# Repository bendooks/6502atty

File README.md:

# 6502 Atty

A 6502 SBC with an ATMega as a contoller and monitor for the 6502.

This is an initial commit as PCBs are off for manufacture and not been tested. This includes the prototype firmware and the first cut of the firmware code.

The ATmega is probably the easiest MCU to get and program which is 5V tolerant. The 1284P is the current choice as the smaller memory versions are not much cheaper.

## Build notes for v1 rev1

- The 100UF capacitors are 16mm long so trying 47uF, layout change?

The LED resistors will probably need to be reduced to 680R or low as 506R depending on the LEDs being fitted.

The pull-up/pull-down resistors can be anywhere from 1K to 4K7, experiments with previous boards show 10K may not be suitable with certain variants of the 6052. Anything below 1K is probably going to have issues with current dissapation as that will be around 5mA per resistor. 

During test it was found that there seems to be a difference in operation dependong on how the PHi2 jumper is selected. If the PHI2O is used, we get proper operation but if CPU_CLK is seleted then the download code works but the code that is downloaded does not work.

## PCB updates (v1 rev2)

- Added J12 to route ~WE signal to the PGM/~WE to allow SRAM
  - Also requires a R/!W signal gated with PHI2 high
  - Added R~{W}ph signal for ROM
  - This new signal could also drive RAM ~WE and connect ~CS to A15
- Connected ROM's VPP signal to GND, if using SRAM, ties A14 to GND
- U9C's pins 9 and 10 swapped for routing
- U11's E1/E2 pins swapped for easier routing
- Transcription error from prototype, ROM_ACC should be from AND not NAND gate
  - Swao U8C for one of U10 spare gates
- RDY line missing pull-up resistor
- 74LS573 replaced with 74LS574
  - 573 latches when Load is high, and our enable is low
  - 574 will load on rising edge of load pin, so should work
- Made PCB smaller, moved a few LEDs and things around to make this work
- Dropped 1K series drive resistor for the crystal
  - ATMega will not start if this resistor is there

TODO:
- Serial converter is rotated 180deg to the actual unit
- Recomendation for AVRisp is to use 10K on ATMega's nRESET, so changed

Currently unknown issues:
- Firmware only works with PHI2 jumper on PHI2out
  - can't see any scoped difference between CPUclk and PHI2out

# Firmware

The firmware is currently in development. To build, you will need at-least avr-gcc and the relevant libraries and is currently only being tested on Linux (Debian). Once built, download to the ATMega using something like avrdude.

## Revision information

The original prototype version was built on a perfboard, and not released.

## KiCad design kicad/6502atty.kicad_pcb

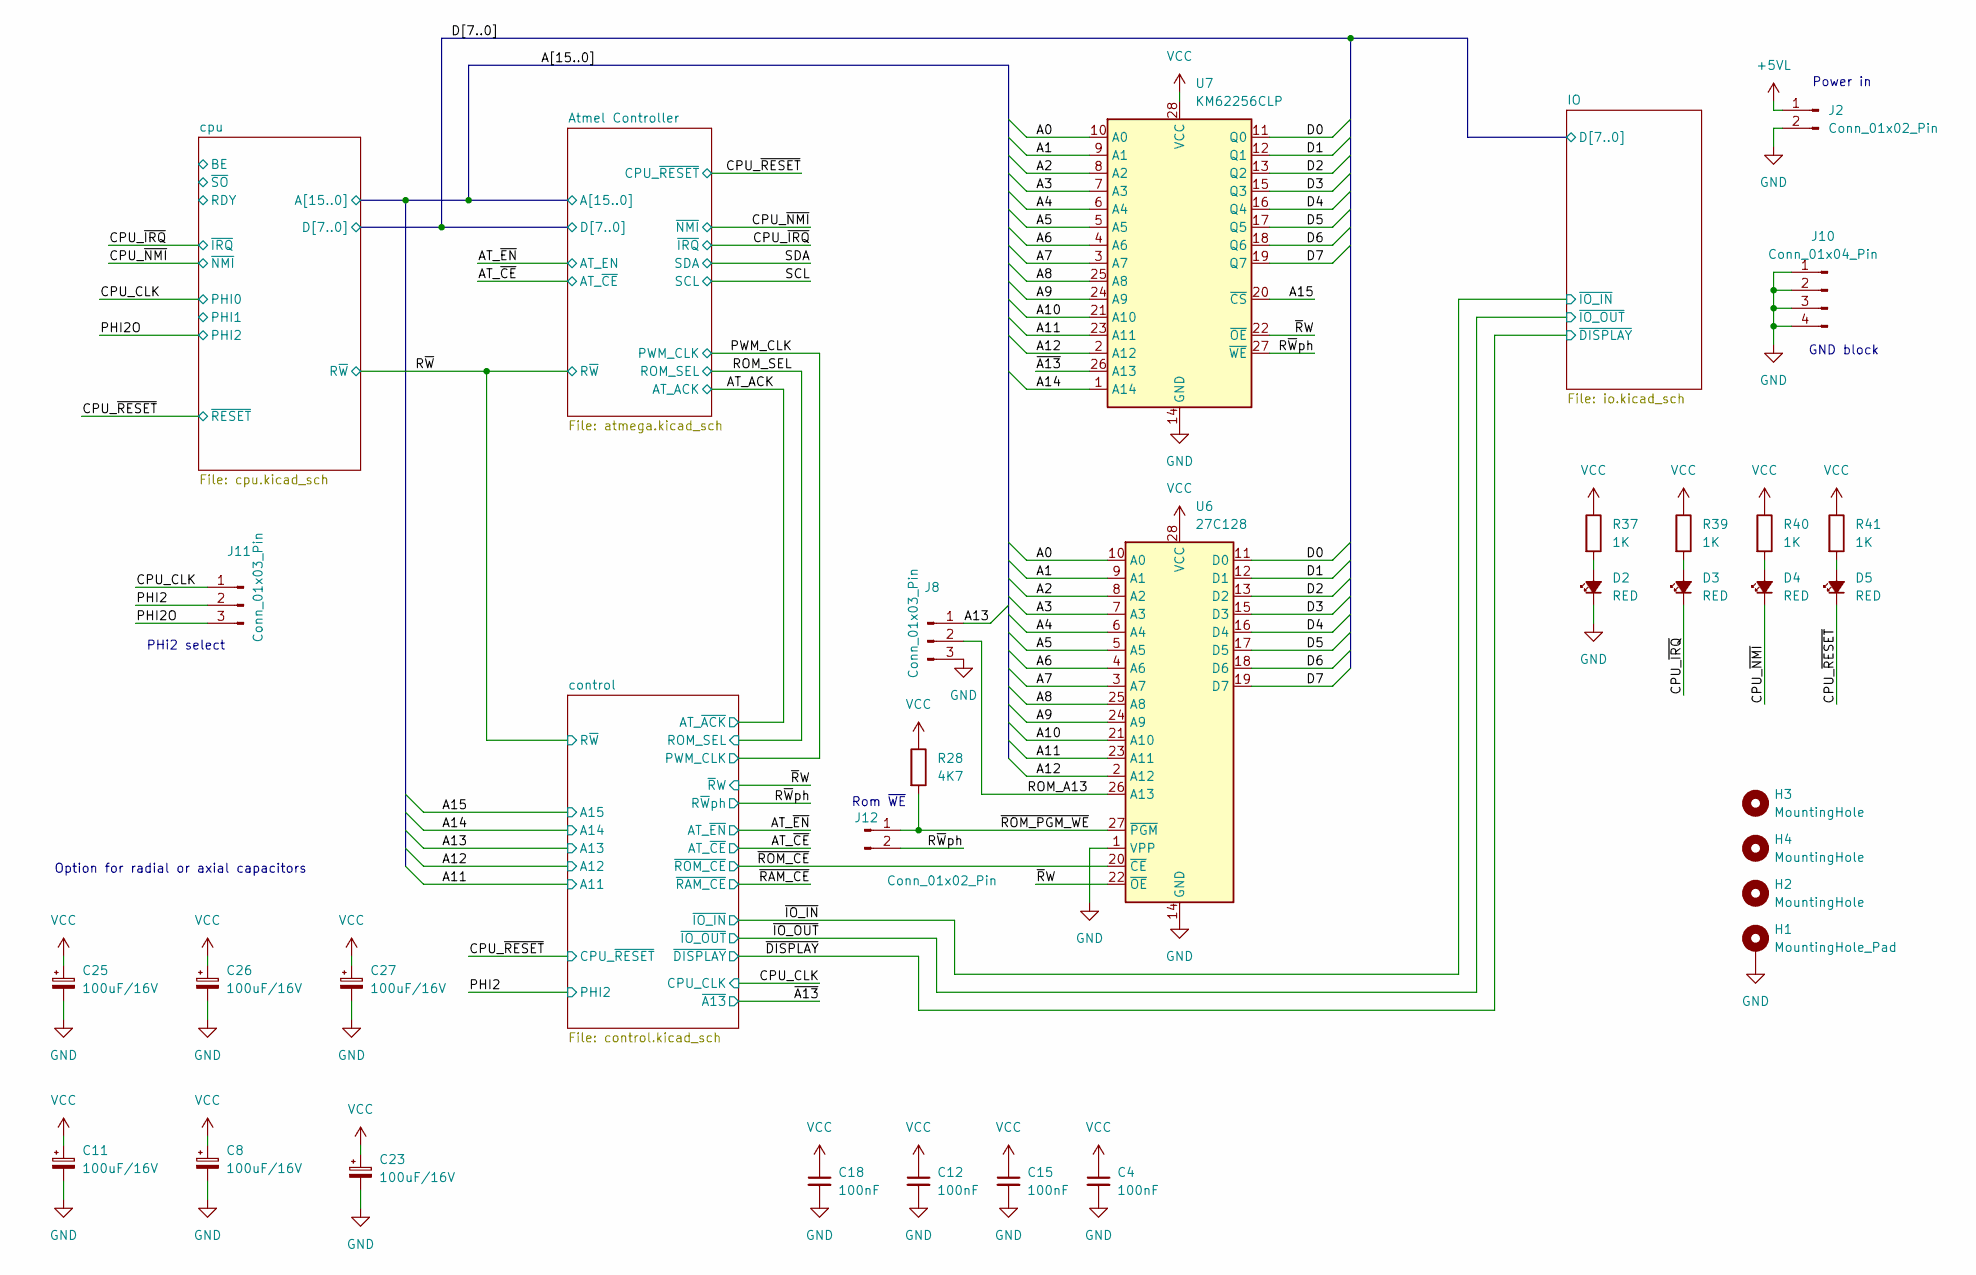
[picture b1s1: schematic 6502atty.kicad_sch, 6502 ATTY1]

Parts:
C4, C12, C15, C18: 100nF; C_Disc_D4.3mm_W1.9mm_P5.00mm
C8, C11, C23: 100uF/16V; CP_Axial_L10.0mm_D6.0mm_P15.00mm_Horizontal
C25, C26, C27: 100uF/16V; CP_Radial_D6.3mm_P2.50mm
D2, D3, D4, D5: RED; LED_D5.0mm
H1: MountingHole_Pad; MountingHole_3.2mm_M3_Pad
H2, H3, H4: MountingHole; MountingHole_3.2mm_M3_Pad
J2: Conn_01x02_Pin; Molex_KK-254_AE-6410-02A_1x02_P2.54mm_Vertical
J8, J11: Conn_01x03_Pin; PinHeader_1x03_P2.54mm_Vertical
J10: Conn_01x04_Pin; PinHeader_1x04_P2.54mm_Vertical
J12: Conn_01x02_Pin; PinHeader_1x02_P2.54mm_Vertical
R28: 4K7; R_Axial_DIN0207_L6.3mm_D2.5mm_P10.16mm_Horizontal
R37, R39, R40: 1K; R_Axial_DIN0207_L6.3mm_D2.5mm_P10.16mm_Horizontal
R41: 1K; R_Axial_DIN0207_L6.3mm_D2.5mm_P2.54mm_Vertical
U6: 27C128; DIP-28_W15.24mm
U7: KM62256CLP; DIP-28_W15.24mm

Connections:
+5VL: J2.1; also elsewhere on the board
/A0: U6.10 (A0), U7.10 (A0); also elsewhere on the board
/A1: U6.9 (A1), U7.9 (A1); also elsewhere on the board
/A2: U6.8 (A2), U7.8 (A2); also elsewhere on the board
/A3: U6.7 (A3), U7.7 (A3); also elsewhere on the board
/A4: U6.6 (A4), U7.6 (A4); also elsewhere on the board
/A5: U6.5 (A5), U7.5 (A5); also elsewhere on the board
/A6: U6.4 (A6), U7.4 (A6); also elsewhere on the board
/A7: U6.3 (A7), U7.3 (A7); also elsewhere on the board
/A8: U6.25 (A8), U7.25 (A8); also elsewhere on the board
/A9: U6.24 (A9), U7.24 (A9); also elsewhere on the board
/A10: U6.21 (A10), U7.21 (A10); also elsewhere on the board
/A11: U6.23 (A11), U7.23 (A11); also elsewhere on the board
/A12: U6.2 (A12), U7.2 (A12); also elsewhere on the board
/A13: J8.1; also elsewhere on the board
/A14: U7.1 (A14); also elsewhere on the board
/A15: U7.20 (~CS); also elsewhere on the board
/CPU_CLK: J11.1; also elsewhere on the board
/CPU_~IRQ: D3.1 (K); also elsewhere on the board
/CPU_~NMI: D4.1 (K); also elsewhere on the board
/CPU_~RESET: D5.1 (K); also elsewhere on the board
/D0: U6.11 (D0), U7.11 (Q0); also elsewhere on the board
/D1: U6.12 (D1), U7.12 (Q1); also elsewhere on the board
/D2: U6.13 (D2), U7.13 (Q2); also elsewhere on the board
/D3: U6.15 (D3), U7.15 (Q3); also elsewhere on the board
/D4: U6.16 (D4), U7.16 (Q4); also elsewhere on the board
/D5: U6.17 (D5), U7.17 (Q5); also elsewhere on the board
/D6: U6.18 (D6), U7.18 (Q6); also elsewhere on the board
/D7: U6.19 (D7), U7.19 (Q7); also elsewhere on the board
/PHI2: J11.2; also elsewhere on the board
/PHI2O: J11.3; also elsewhere on the board
/ROM_A13: J8.2, U6.26 (A13)
/R~Wph: J12.2, U7.27 (~WE); also elsewhere on the board
/~A13: U7.26 (A13); also elsewhere on the board
/~ROM_CE: U6.20 (~CE); also elsewhere on the board
/~ROM_PGM_WE: J12.1, R28.2, U6.27 (~PGM)
/~RW: U6.22 (~OE), U7.22 (~OE); also elsewhere on the board
GND: C4.2, C8.2, C11.2, C12.2, C15.2, C18.2, C23.2, C25.2, C26.2, C27.2, D2.1 (K), H1.1, J2.2, J8.3, J10.1, J10.2, J10.3, J10.4, U6.1 (VPP), U6.14 (GND), U7.14 (GND); also elsewhere on the board
unnamed: D2.2 (A), R37.2
unnamed: D3.2 (A), R39.2
unnamed: D4.2 (A), R40.2
unnamed: D5.2 (A), R41.2
VCC: C4.1, C8.1, C11.1, C12.1, C15.1, C18.1, C23.1, C25.1, C26.1, C27.1, R28.1, R37.1, R39.1, R40.1, R41.1, U6.28 (VCC), U7.28 (VCC); also elsewhere on the board

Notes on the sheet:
Power in
GND block
Option for radial or axial capacitors
PHi2 select
Rom ~{WE}

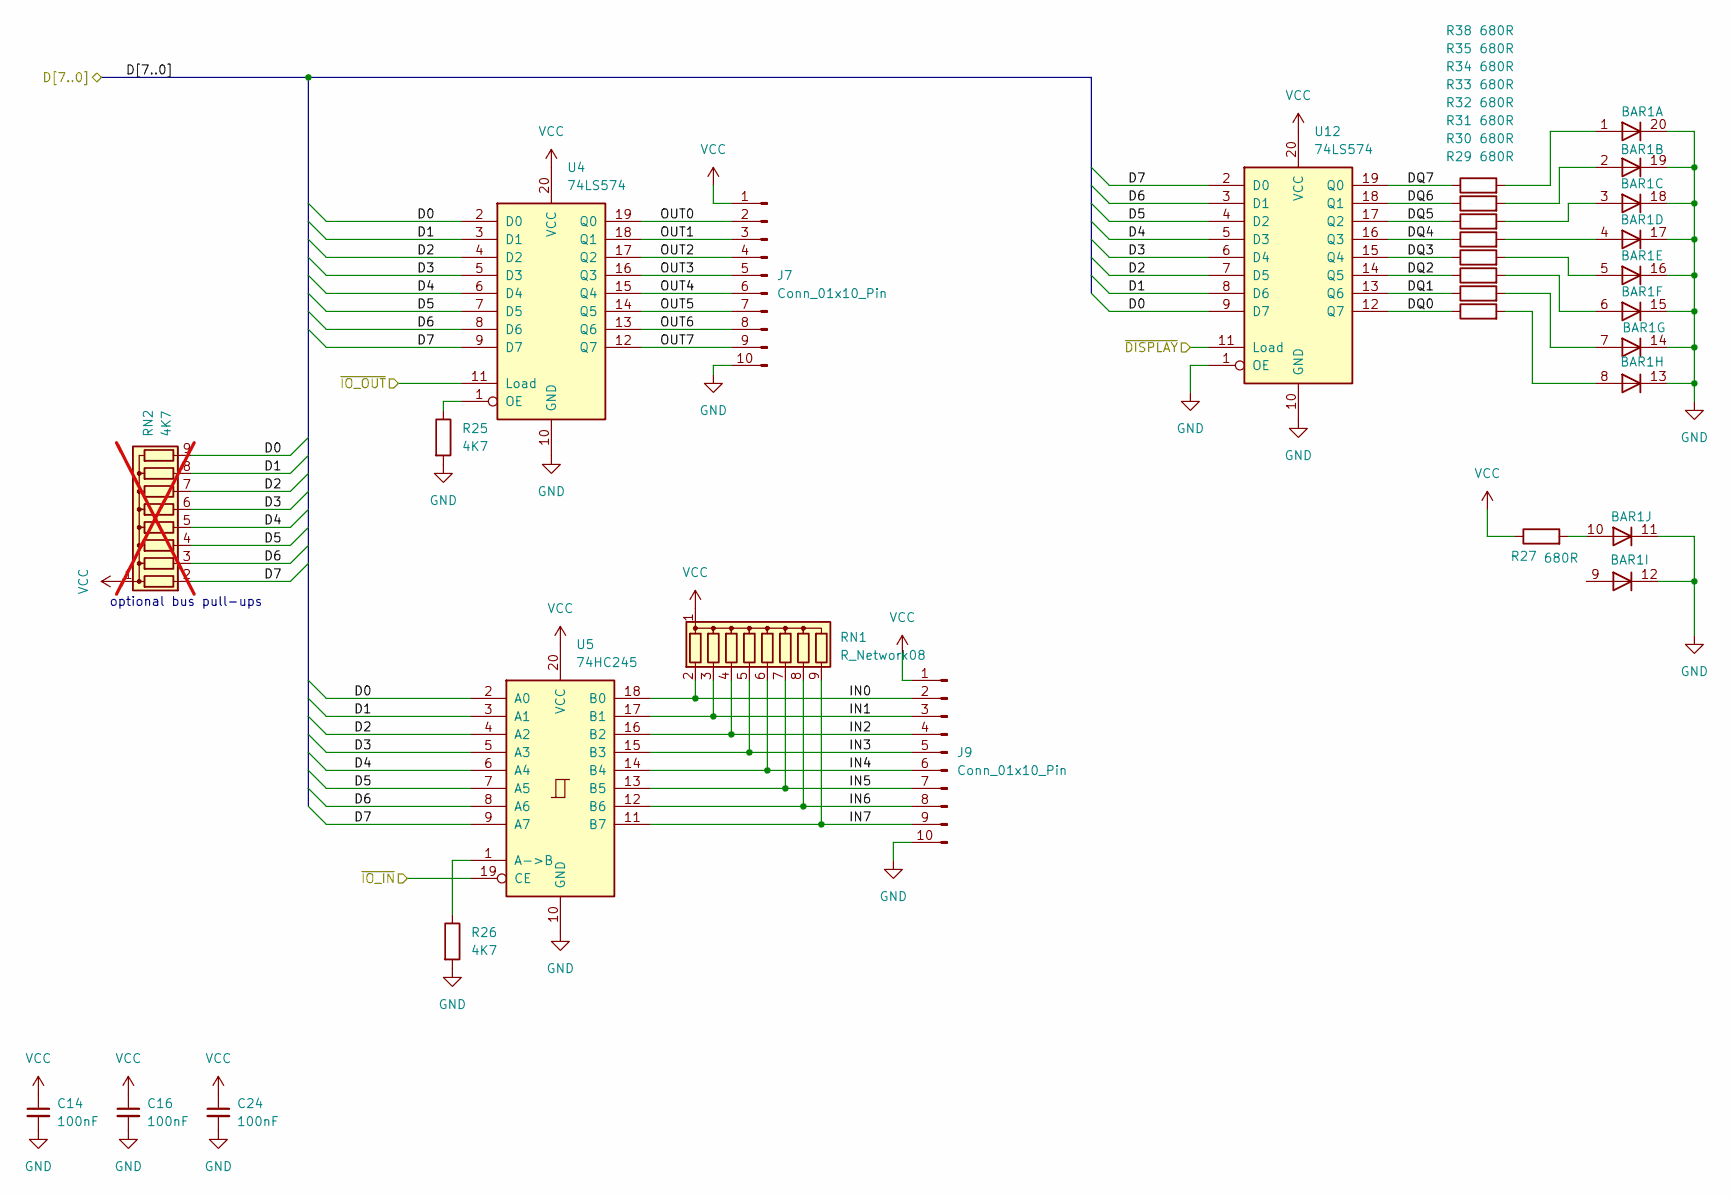
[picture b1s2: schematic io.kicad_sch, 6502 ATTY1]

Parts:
BAR1: HDSP-4850
C14, C16, C24: 100nF; C_Disc_D4.3mm_W1.9mm_P5.00mm
J7, J9: Conn_01x10_Pin; PinHeader_1x10_P2.54mm_Vertical
R25, R26: 4K7; R_Axial_DIN0207_L6.3mm_D2.5mm_P10.16mm_Horizontal
R27, R29, R30, R31, R32, R33, R34, R35, R38: 680R; R_Axial_DIN0207_L6.3mm_D2.5mm_P2.54mm_Vertical
RN1: R_Network08; R_Array_SIP9
RN2: 4K7; R_Array_SIP9; not fitted
U4, U12: 74LS574; DIP-20_W7.62mm
U5: 74HC245; DIP-20_W7.62mm

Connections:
/D0: RN2.9 (R8), U4.2 (D0), U5.2 (A0), U12.9 (D7); also elsewhere on the board
/D1: RN2.8 (R7), U4.3 (D1), U5.3 (A1), U12.8 (D6); also elsewhere on the board
/D2: RN2.7 (R6), U4.4 (D2), U5.4 (A2), U12.7 (D5); also elsewhere on the board
/D3: RN2.6 (R5), U4.5 (D3), U5.5 (A3), U12.6 (D4); also elsewhere on the board
/D4: RN2.5 (R4), U4.6 (D4), U5.6 (A4), U12.5 (D3); also elsewhere on the board
/D5: RN2.4 (R3), U4.7 (D5), U5.7 (A5), U12.4 (D2); also elsewhere on the board
/D6: RN2.3 (R2), U4.8 (D6), U5.8 (A6), U12.3 (D1); also elsewhere on the board
/D7: RN2.2 (R1), U4.9 (D7), U5.9 (A7), U12.2 (D0); also elsewhere on the board
/IO/DQ0: R29.1, U12.12 (Q7)
/IO/DQ1: R30.1, U12.13 (Q6)
/IO/DQ2: R31.1, U12.14 (Q5)
/IO/DQ3: R32.1, U12.15 (Q4)
/IO/DQ4: R33.1, U12.16 (Q3)
/IO/DQ5: R34.1, U12.17 (Q2)
/IO/DQ6: R35.1, U12.18 (Q1)
/IO/DQ7: R38.1, U12.19 (Q0)
/IO/IN0: J9.2, RN1.2 (R1), U5.18 (B0)
/IO/IN1: J9.3, RN1.3 (R2), U5.17 (B1)
/IO/IN2: J9.4, RN1.4 (R3), U5.16 (B2)
/IO/IN3: J9.5, RN1.5 (R4), U5.15 (B3)
/IO/IN4: J9.6, RN1.6 (R5), U5.14 (B4)
/IO/IN5: J9.7, RN1.7 (R6), U5.13 (B5)
/IO/IN6: J9.8, RN1.8 (R7), U5.12 (B6)
/IO/IN7: J9.9, RN1.9 (R8), U5.11 (B7)
/IO/OUT0: J7.2, U4.19 (Q0)
/IO/OUT1: J7.3, U4.18 (Q1)
/IO/OUT2: J7.4, U4.17 (Q2)
/IO/OUT3: J7.5, U4.16 (Q3)
/IO/OUT4: J7.6, U4.15 (Q4)
/IO/OUT5: J7.7, U4.14 (Q5)
/IO/OUT6: J7.8, U4.13 (Q6)
/IO/OUT7: J7.9, U4.12 (Q7)
/~DISPLAY: U12.11 (Load); also elsewhere on the board
/~IO_IN: U5.19 (CE); also elsewhere on the board
/~IO_OUT: U4.11 (Load); also elsewhere on the board
GND: BAR1.11 (K), BAR1.12 (K), BAR1.13 (K), BAR1.14 (K), BAR1.15 (K), BAR1.16 (K), BAR1.17 (K), BAR1.18 (K), BAR1.19 (K), BAR1.20 (K), C14.2, C16.2, C24.2, J7.10, J9.10, R25.2, R26.2, U4.10 (GND), U5.10 (GND), U12.1 (OE), U12.10 (GND); also elsewhere on the board
unnamed: BAR1.1 (A), R38.2
unnamed: BAR1.2 (A), R35.2
unnamed: BAR1.3 (A), R34.2
unnamed: BAR1.4 (A), R33.2
unnamed: BAR1.5 (A), R32.2
unnamed: BAR1.6 (A), R31.2
unnamed: BAR1.7 (A), R30.2
unnamed: BAR1.8 (A), R29.2
unnamed: BAR1.10 (A), R27.2
unnamed: R25.1, U4.1 (OE)
unnamed: R26.1, U5.1 (A->B)
VCC: C14.1, C16.1, C24.1, J7.1, J9.1, R27.1, RN1.1 (common), RN2.1 (common), U4.20 (VCC), U5.20 (VCC), U12.20 (VCC); also elsewhere on the board

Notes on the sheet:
optional bus pull-ups

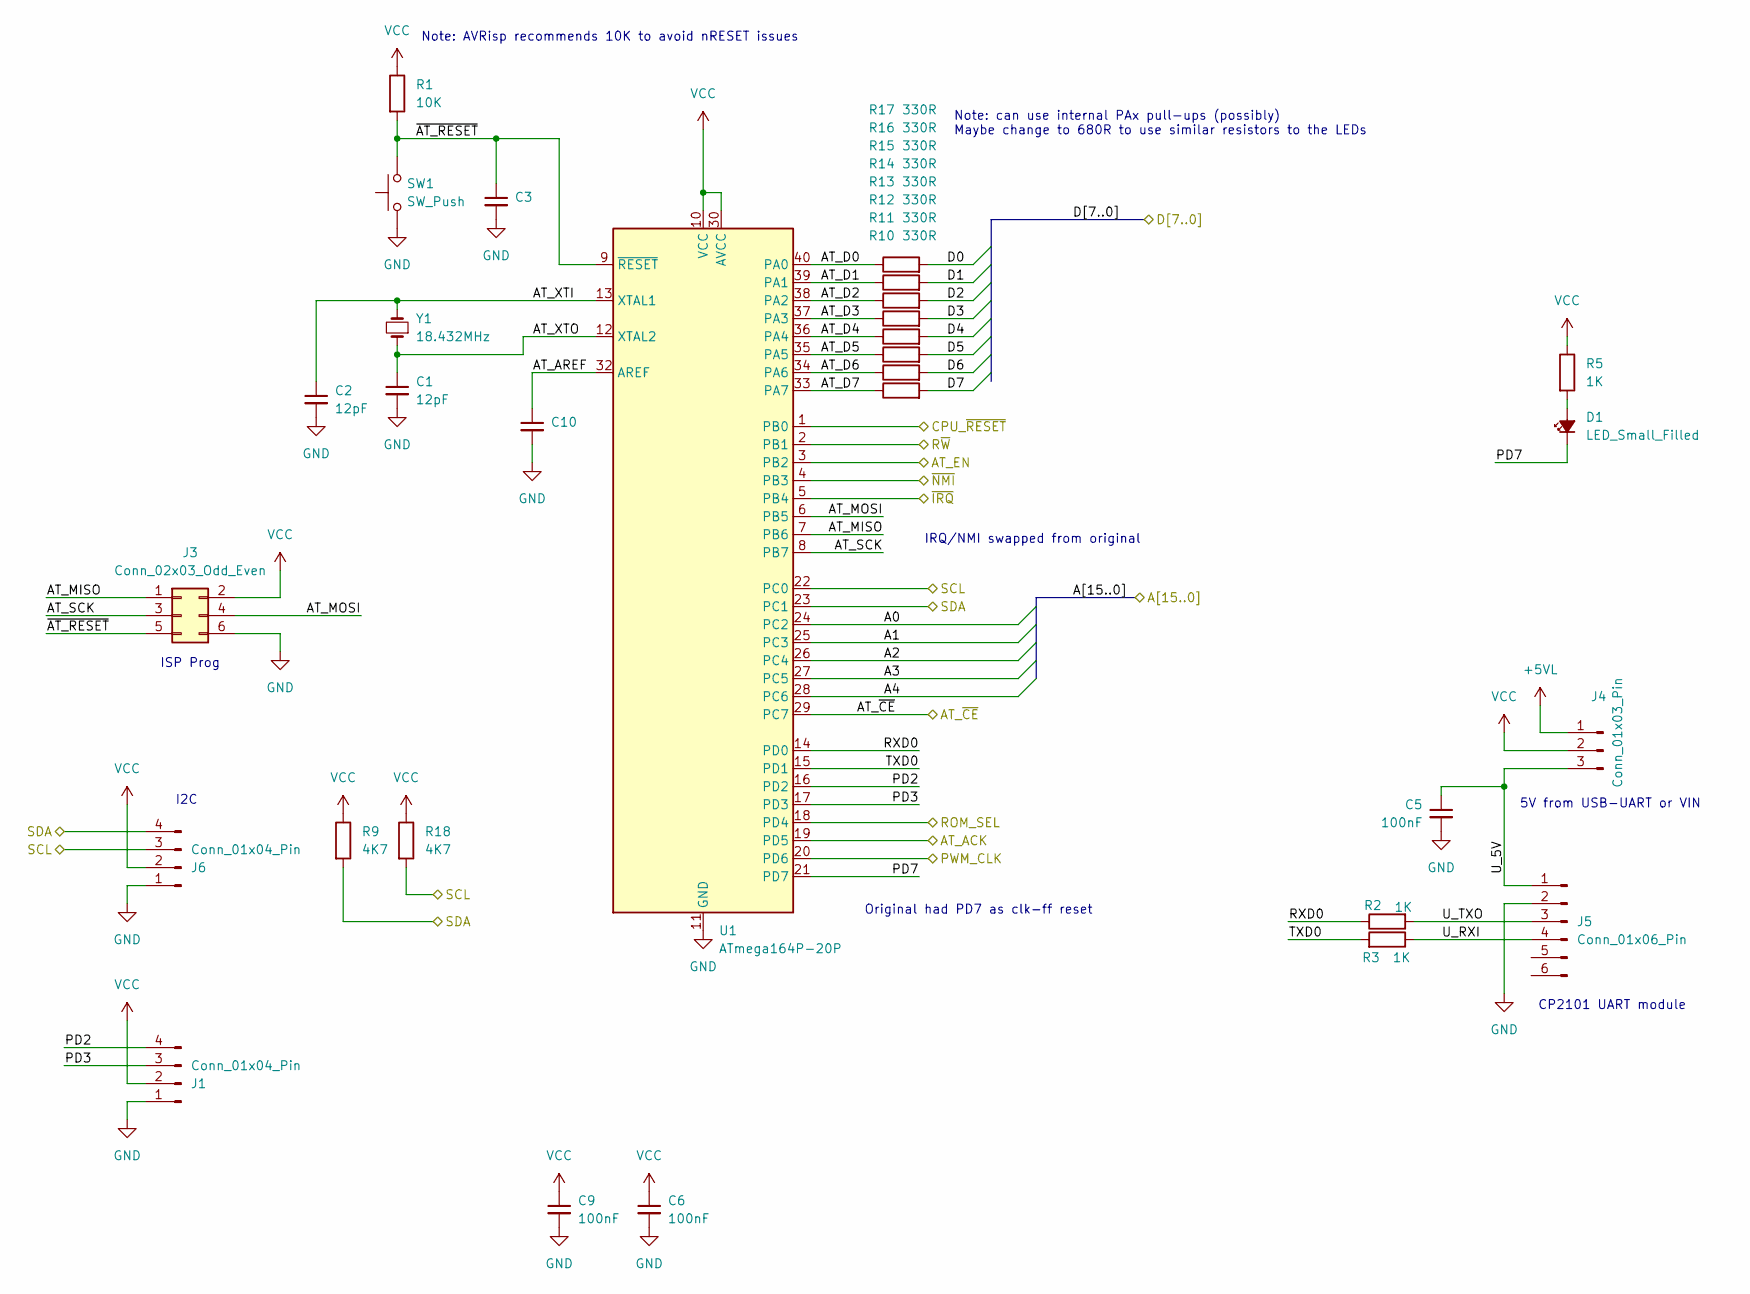
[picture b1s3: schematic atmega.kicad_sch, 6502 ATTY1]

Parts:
C1, C2: 12pF; C_Disc_D3.4mm_W2.1mm_P2.50mm
C3, C10: C_Disc_D4.3mm_W1.9mm_P5.00mm
C5, C6, C9: 100nF; C_Disc_D4.3mm_W1.9mm_P5.00mm
D1: LED_Small_Filled; LED_D5.0mm
J1: Conn_01x04_Pin; PinHeader_1x04_P2.54mm_Vertical
J3: Conn_02x03_Odd_Even; PinHeader_2x03_P2.54mm_Vertical
J4: Conn_01x03_Pin; PinHeader_1x03_P2.54mm_Vertical
J5: Conn_01x06_Pin; PinHeader_1x06_P2.54mm_Vertical
J6: Conn_01x04_Pin; PinSocket_1x04_P2.54mm_Vertical
R1: 10K; R_Axial_DIN0207_L6.3mm_D2.5mm_P2.54mm_Vertical
R2, R3, R5: 1K; R_Axial_DIN0207_L6.3mm_D2.5mm_P10.16mm_Horizontal
R9, R18: 4K7; R_Axial_DIN0207_L6.3mm_D2.5mm_P10.16mm_Horizontal
R10, R11, R12, R13, R14, R15, R16, R17: 330R; R_Axial_DIN0207_L6.3mm_D2.5mm_P10.16mm_Horizontal
SW1: SW_Push; SW_TH_Tactile_Omron_B3F-10xx
U1: ATmega164P-20P; DIP-40_W15.24mm
Y1: 18.432MHz; Crystal_HC49-4H_Vertical

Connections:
+5VL: J4.1; also elsewhere on the board
/A0: U1.24 (PC2); also elsewhere on the board
/A1: U1.25 (PC3); also elsewhere on the board
/A2: U1.26 (PC4); also elsewhere on the board
/A3: U1.27 (PC5); also elsewhere on the board
/A4: U1.28 (PC6); also elsewhere on the board
/AT_ACK: U1.19 (PD5); also elsewhere on the board
/AT_~CE: U1.29 (PC7); also elsewhere on the board
/AT_~EN: U1.3 (PB2); also elsewhere on the board
/Atmel Controller/AT_AREF: C10.1, U1.32 (AREF)
/Atmel Controller/AT_D0: R17.1, U1.40 (PA0)
/Atmel Controller/AT_D1: R16.1, U1.39 (PA1)
/Atmel Controller/AT_D2: R15.1, U1.38 (PA2)
/Atmel Controller/AT_D3: R14.1, U1.37 (PA3)
/Atmel Controller/AT_D4: R13.1, U1.36 (PA4)
/Atmel Controller/AT_D5: R12.1, U1.35 (PA5)
/Atmel Controller/AT_D6: R11.1, U1.34 (PA6)
/Atmel Controller/AT_D7: R10.1, U1.33 (PA7)
/Atmel Controller/AT_MISO: J3.1, U1.7 (PB6)
/Atmel Controller/AT_MOSI: J3.4, U1.6 (PB5)
/Atmel Controller/AT_SCK: J3.3, U1.8 (PB7)
/Atmel Controller/AT_XTI: C2.1, U1.13 (XTAL1), Y1.2
/Atmel Controller/AT_XTO: C1.1, U1.12 (XTAL2), Y1.1
/Atmel Controller/PD2: J1.4, U1.16 (PD2)
/Atmel Controller/PD3: J1.3, U1.17 (PD3)
/Atmel Controller/PD7: D1.1 (K), U1.21 (PD7)
/Atmel Controller/RXD0: R2.1, U1.14 (PD0)
/Atmel Controller/TXD0: R3.2, U1.15 (PD1)
/Atmel Controller/U_5V: C5.1, J4.3, J5.1
/Atmel Controller/U_RXI: J5.4, R3.1
/Atmel Controller/U_TXO: J5.3, R2.2
/Atmel Controller/~AT_RESET: C3.1, J3.5, R1.2, SW1.2, U1.9 (~RESET)
/CPU_~IRQ: U1.5 (PB4); also elsewhere on the board
/CPU_~NMI: U1.4 (PB3); also elsewhere on the board
/CPU_~RESET: U1.1 (PB0); also elsewhere on the board
/D0: R17.2; also elsewhere on the board
/D1: R16.2; also elsewhere on the board
/D2: R15.2; also elsewhere on the board
/D3: R14.2; also elsewhere on the board
/D4: R13.2; also elsewhere on the board
/D5: R12.2; also elsewhere on the board
/D6: R11.2; also elsewhere on the board
/D7: R10.2; also elsewhere on the board
/PWM_CLK: U1.20 (PD6); also elsewhere on the board
/ROM_SEL: U1.18 (PD4); also elsewhere on the board
/R~W: U1.2 (PB1); also elsewhere on the board
/SCL: J6.3, R18.2, U1.22 (PC0)
/SDA: J6.4, R9.2, U1.23 (PC1)
GND: C1.2, C2.2, C3.2, C5.2, C6.2, C9.2, C10.2, J1.1, J3.6, J5.2, J6.1, SW1.1, U1.11 (GND), U1.31 (GND); also elsewhere on the board
unnamed: D1.2 (A), R5.2
VCC: C6.1, C9.1, J1.2, J3.2, J4.2, J6.2, R1.1, R5.1, R9.1, R18.1, U1.10 (VCC), U1.30 (AVCC); also elsewhere on the board

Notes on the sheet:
ISP Prog
I2C
5V from USB-UART or VIN
Original had PD7 as clk-ff reset
IRQ/NMI swapped from original
Note: can use internal PAx pull-ups (possibly) Maybe change to 680R to use similar resistors to the LEDs
CP2101 UART module
Note: AVRisp recommends 10K to avoid nRESET issues

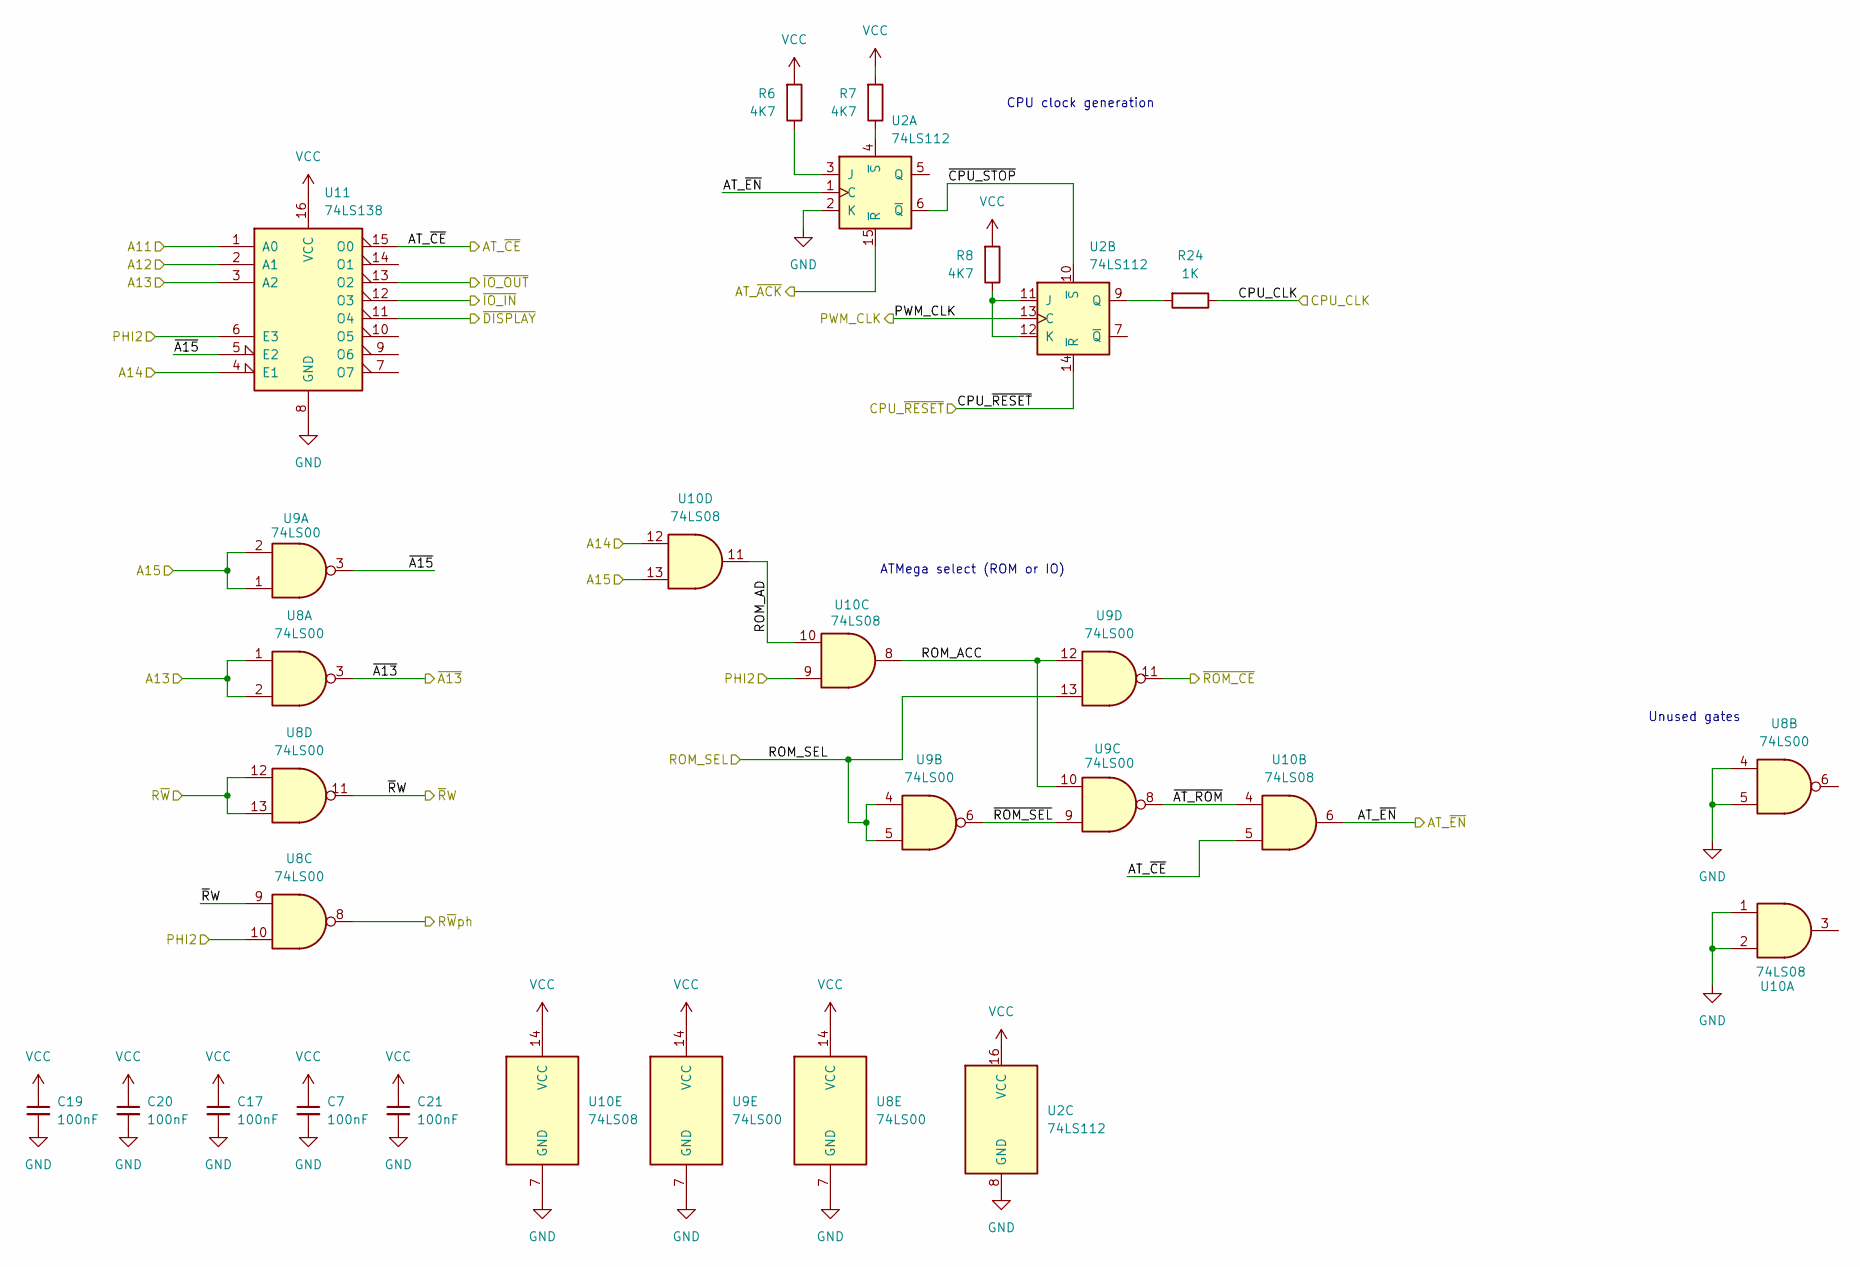
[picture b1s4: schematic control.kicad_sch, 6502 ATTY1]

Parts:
C7, C17, C19, C20, C21: 100nF; C_Disc_D4.3mm_W1.9mm_P5.00mm
R6, R7, R8: 4K7; R_Axial_DIN0207_L6.3mm_D2.5mm_P10.16mm_Horizontal
R24: 1K; R_Axial_DIN0207_L6.3mm_D2.5mm_P10.16mm_Horizontal
U2: 74LS112; DIP-16_W7.62mm
U8, U9: 74LS00; DIP-14_W7.62mm
U10: 74LS08; DIP-14_W7.62mm
U11: 74LS138; DIP-16_W7.62mm

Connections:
/A11: U11.1 (A0); also elsewhere on the board
/A12: U11.2 (A1); also elsewhere on the board
/A13: U8.1, U8.2, U11.3 (A2); also elsewhere on the board
/A14: U10.12, U11.4 (E1); also elsewhere on the board
/A15: U9.1, U9.2, U10.13; also elsewhere on the board
/AT_ACK: U2.15 (~R); also elsewhere on the board
/AT_~CE: U10.5, U11.15 (O0); also elsewhere on the board
/AT_~EN: U2.1 (C), U10.6; also elsewhere on the board
/CPU_CLK: R24.1; also elsewhere on the board
/CPU_~RESET: U2.14 (~R); also elsewhere on the board
/PHI2: U8.10, U10.9, U11.6 (E3); also elsewhere on the board
/PWM_CLK: U2.13 (C); also elsewhere on the board
/ROM_SEL: U9.4, U9.5, U9.13; also elsewhere on the board
/R~W: U8.12, U8.13; also elsewhere on the board
/R~Wph: U8.8; also elsewhere on the board
/control/ROM_ACC: U9.10, U9.12, U10.8
/control/ROM_AD: U10.10, U10.11
/control/~A15: U9.3, U11.5 (E2)
/control/~AT_ROM: U9.8, U10.4
/control/~CPU_STOP: U2.6 (~Q), U2.10 (~S)
/control/~ROM_SEL: U9.6, U9.9
/~A13: U8.3; also elsewhere on the board
/~DISPLAY: U11.11 (O4); also elsewhere on the board
/~IO_IN: U11.12 (O3); also elsewhere on the board
/~IO_OUT: U11.13 (O2); also elsewhere on the board
/~ROM_CE: U9.11; also elsewhere on the board
/~RW: U8.9, U8.11; also elsewhere on the board
GND: C7.2, C17.2, C19.2, C20.2, C21.2, U2.2 (K), U2.8 (GND), U8.4, U8.5, U8.7 (GND), U9.7 (GND), U10.1, U10.2, U10.7 (GND), U11.8 (GND); also elsewhere on the board
unnamed: R6.1, U2.3 (J)
unnamed: R7.1, U2.4 (~S)
unnamed: R8.1, U2.11 (J), U2.12 (K)
unnamed: R24.2, U2.9 (Q)
VCC: C7.1, C17.1, C19.1, C20.1, C21.1, R6.2, R7.2, R8.2, U2.16 (VCC), U8.14 (VCC), U9.14 (VCC), U10.14 (VCC), U11.16 (VCC); also elsewhere on the board

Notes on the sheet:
ATMega select (ROM or IO)
Unused gates
CPU clock generation

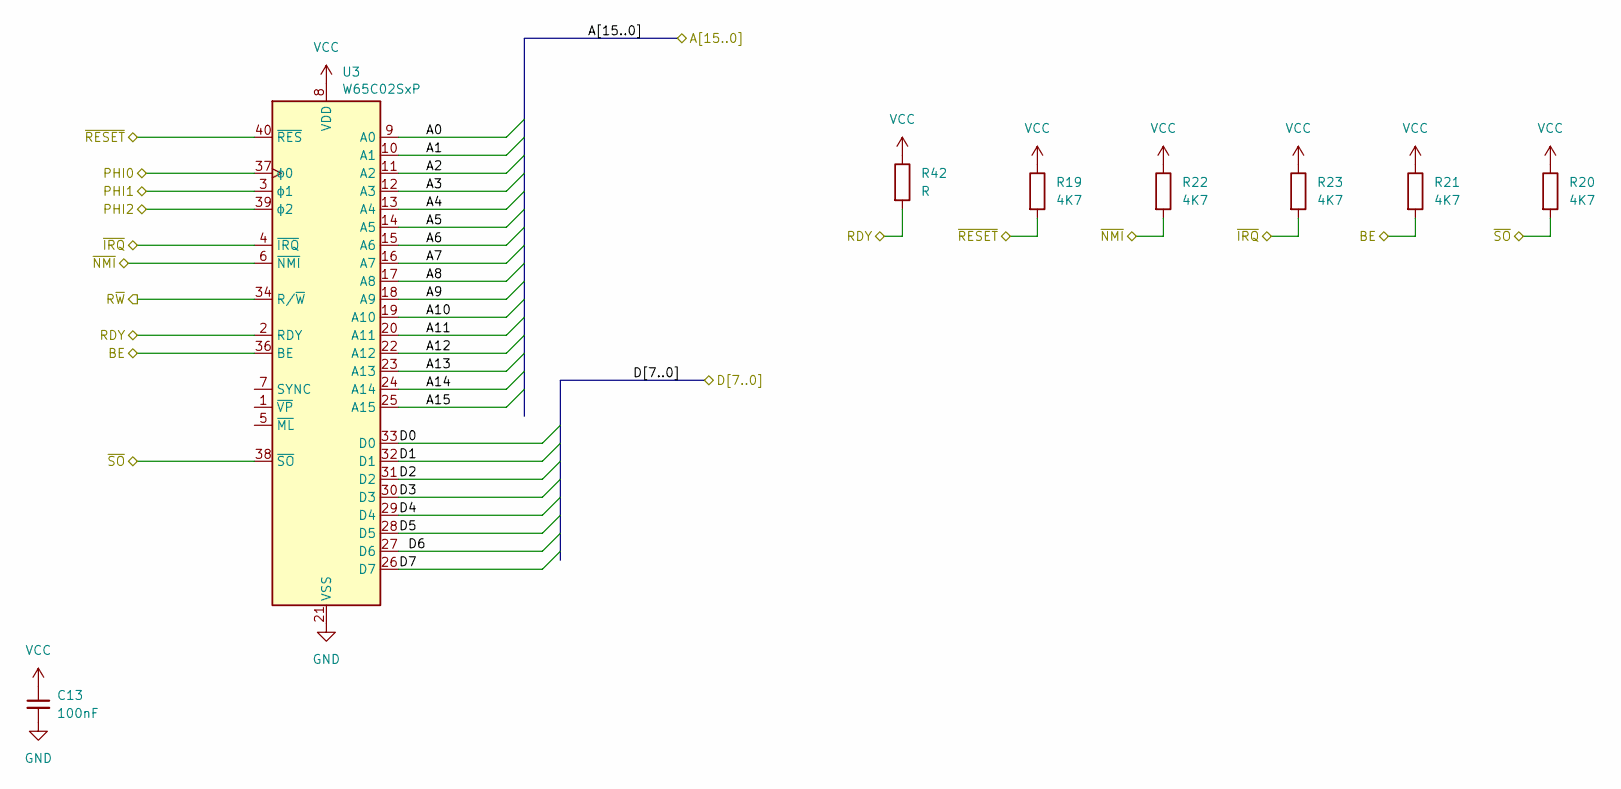
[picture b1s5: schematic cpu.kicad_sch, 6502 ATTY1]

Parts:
C13: 100nF; C_Disc_D4.3mm_W1.9mm_P5.00mm
R19, R20, R21, R22, R23: 4K7; R_Axial_DIN0207_L6.3mm_D2.5mm_P10.16mm_Horizontal
R42: R; R_Axial_DIN0207_L6.3mm_D2.5mm_P10.16mm_Horizontal
U3: W65C02SxP; DIP-40_W15.24mm

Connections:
/A0: U3.9 (A0); also elsewhere on the board
/A1: U3.10 (A1); also elsewhere on the board
/A2: U3.11 (A2); also elsewhere on the board
/A3: U3.12 (A3); also elsewhere on the board
/A4: U3.13 (A4); also elsewhere on the board
/A5: U3.14 (A5); also elsewhere on the board
/A6: U3.15 (A6); also elsewhere on the board
/A7: U3.16 (A7); also elsewhere on the board
/A8: U3.17 (A8); also elsewhere on the board
/A9: U3.18 (A9); also elsewhere on the board
/A10: U3.19 (A10); also elsewhere on the board
/A11: U3.20 (A11); also elsewhere on the board
/A12: U3.22 (A12); also elsewhere on the board
/A13: U3.23 (A13); also elsewhere on the board
/A14: U3.24 (A14); also elsewhere on the board
/A15: U3.25 (A15); also elsewhere on the board
/CPU_CLK: U3.37 (ϕ0); also elsewhere on the board
/CPU_~IRQ: R23.2, U3.4 (~IRQ); also elsewhere on the board
/CPU_~NMI: R22.2, U3.6 (~NMI); also elsewhere on the board
/CPU_~RESET: R19.2, U3.40 (~RES); also elsewhere on the board
/D0: U3.33 (D0); also elsewhere on the board
/D1: U3.32 (D1); also elsewhere on the board
/D2: U3.31 (D2); also elsewhere on the board
/D3: U3.30 (D3); also elsewhere on the board
/D4: U3.29 (D4); also elsewhere on the board
/D5: U3.28 (D5); also elsewhere on the board
/D6: U3.27 (D6); also elsewhere on the board
/D7: U3.26 (D7); also elsewhere on the board
/PHI2O: U3.39 (ϕ2); also elsewhere on the board
/R~W: U3.34 (R/~W); also elsewhere on the board
/cpu/BE: R21.2, U3.36 (BE)
/cpu/PHI1: U3.3 (ϕ1)
/cpu/RDY: R42.2, U3.2 (RDY)
/cpu/~SO: R20.2, U3.38 (~SO)
GND: C13.2, U3.21 (VSS); also elsewhere on the board
VCC: C13.1, R19.1, R20.1, R21.1, R22.1, R23.1, R42.1, U3.8 (VDD); also elsewhere on the board

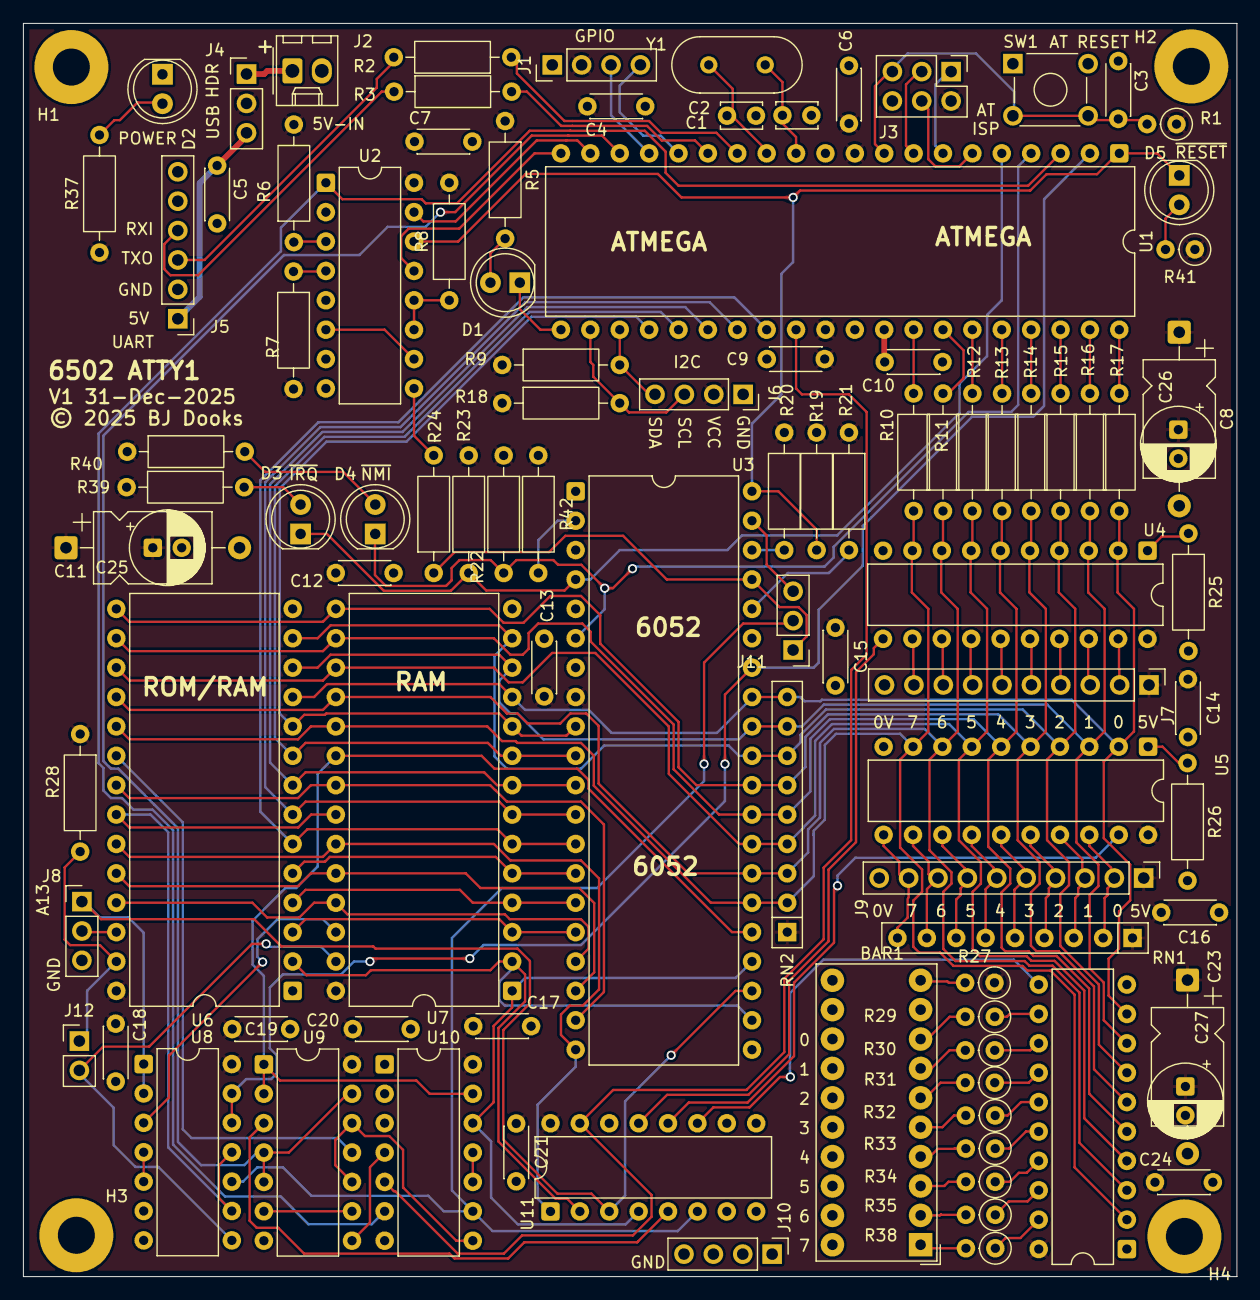
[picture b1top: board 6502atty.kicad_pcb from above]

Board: 2 copper layers, 104.9 x 108.3 mm, 104 parts (0 on the bottom side), 126 nets.

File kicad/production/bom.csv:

Designator,Footprint,Quantity,Value,LCSC Part #
BAR1,HDSP-4850,1,HDSP-4850,
"C1, C2",C_Disc_D3.4mm_W2.1mm_P2.50mm,2,12pF,
"C10, C3",C_Disc_D4.3mm_W1.9mm_P5.00mm,2,~,
"C11, C22, C23, C8",CP_Axial_L10.0mm_D6.0mm_P15.00mm_Horizontal,4,100uF/16V,
"C12, C13, C14, C15, C16, C17, C18, C19, C20, C21, C24, C4, C5, C6, C7, C9",C_Disc_D4.3mm_W1.9mm_P5.00mm,16,100nF,
D1,LED_D5.0mm,1,LED_Small_Filled,
"D2, D3, D4, D5",LED_D5.0mm,4,RED,
"J1, J10",PinHeader_1x04_P2.54mm_Vertical,2,Conn_01x04_Pin,
"J11, J4, J8",PinHeader_1x03_P2.54mm_Vertical,3,Conn_01x03_Pin,
J12,PinHeader_1x02_P2.54mm_Vertical,1,Conn_01x02_Pin,
J2,Molex_KK-254_AE-6410-02A_1x02_P2.54mm_Vertical,1,Conn_01x02_Pin,
J3,PinHeader_2x03_P2.54mm_Vertical,1,Conn_02x03_Odd_Even,
J5,PinHeader_1x06_P2.54mm_Vertical,1,Conn_01x06_Pin,
J6,PinSocket_1x04_P2.54mm_Vertical,1,Conn_01x04_Pin,
"J7, J9",PinHeader_1x10_P2.54mm_Vertical,2,Conn_01x10_Pin,
"R1, R2, R24, R3, R37, R39, R4, R40, R5",R_Axial_DIN0207_L6.3mm_D2.5mm_P10.16mm_Horizontal,9,1K,
"R10, R11, R12, R13, R14, R15, R16, R17",R_Axial_DIN0207_L6.3mm_D2.5mm_P10.16mm_Horizontal,8,330R,
"R18, R19, R20, R21, R22, R23, R25, R26, R28, R6, R7, R8, R9",R_Axial_DIN0207_L6.3mm_D2.5mm_P10.16mm_Horizontal,13,4K7,
"R27, R29, R30, R31, R32, R33, R34, R35, R38",R_Axial_DIN0207_L6.3mm_D2.5mm_P2.54mm_Vertical,9,680R,
R41,R_Axial_DIN0207_L6.3mm_D2.5mm_P2.54mm_Vertical,1,1K,
R42,R_Axial_DIN0207_L6.3mm_D2.5mm_P10.16mm_Horizontal,1,R,
RN1,R_Array_SIP9,1,R_Network08,
RN2,R_Array_SIP9,1,4K7,
SW1,SW_TH_Tactile_Omron_B3F-10xx,1,SW_Push,
U1,DIP-40_W15.24mm,1,ATmega164P-20P,
U10,DIP-14_W7.62mm,1,74LS08,
U11,DIP-16_W7.62mm,1,74LS138,
"U12, U4",DIP-20_W7.62mm,2,74LS574,
U2,DIP-16_W7.62mm,1,74LS112,
U3,DIP-40_W15.24mm,1,W65C02SxP,
U5,DIP-20_W7.62mm,1,74HC245,
U6,DIP-28_W15.24mm,1,27C128,
U7,DIP-28_W15.24mm,1,KM62256CLP,
"U8, U9",DIP-14_W7.62mm,2,74LS00,
Y1,Crystal_HC49-4H_Vertical,1,18.432MHz,

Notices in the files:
kicad/6502atty.kicad_pcb:
© 2025 BJ Dooks
kicad/6502atty.kicad_sch:
© 2025 Ben Dooks
